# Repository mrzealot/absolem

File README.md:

# Absolem

A flat, minimalistic, ergonomic, 36-key keyboard layout.
Read about it at the [intro blogpost](https://zealot.hu/absolem), or come join the [Discord "clubhouse"](https://discord.gg/DbCfZfZ)!

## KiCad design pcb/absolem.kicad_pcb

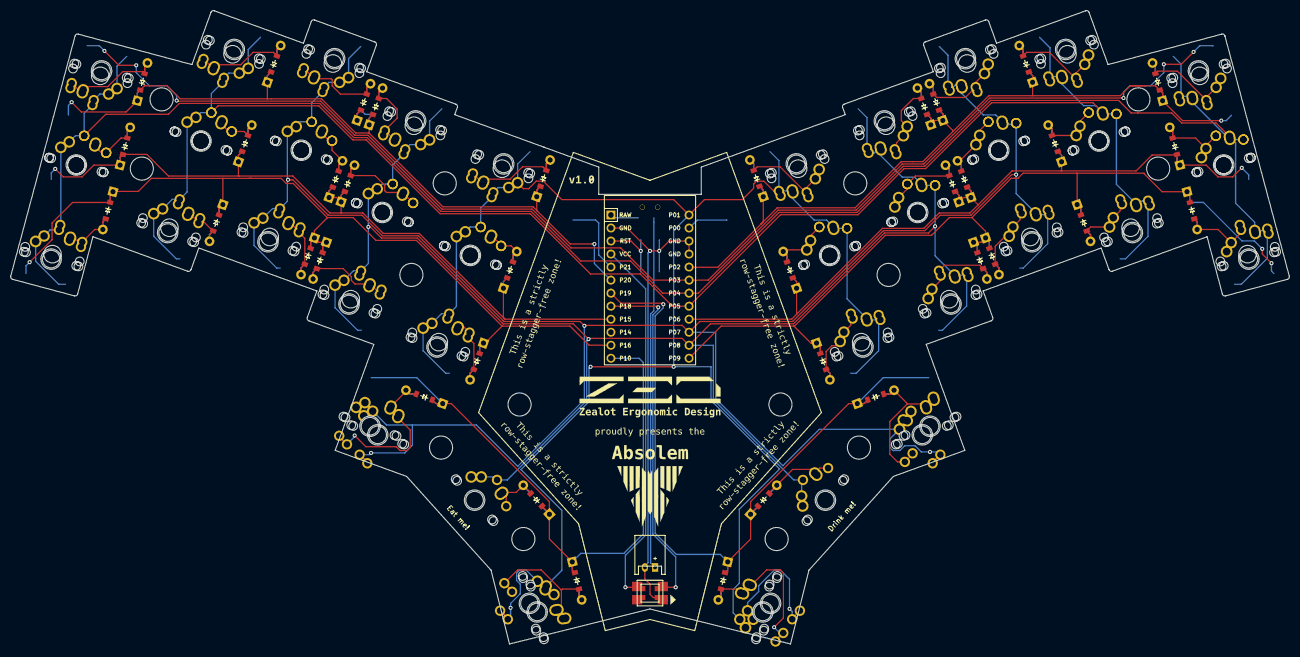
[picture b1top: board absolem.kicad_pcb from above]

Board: 2 copper layers, 249.4 x 123.5 mm, 225 parts (0 on the bottom side), 58 nets.

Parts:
B1: SW_TACT_ALPS_SKQGABE010
C1: ProMicro
D1, D2, D3, D4, D5, D6, D7, D8, D9, D10, D11, D12, D13, D14, D15, D16, D17, D18, D19, D20, D21, D22, D23, D24, D25, D26, D27, D28, D29, D30, D31, D32, D33, D34, D35, D36: ComboDiode
GBACK: LOGO
GFRONT: LOGO
J1: JST_PH_S2B-PH-K_02x2.00mm_Angled
L1: WS2812B
P1, P2, P3, P4, P5, P6, P7, P8, P9, P10, P11, P12, P13, P14, P15, P16, P17, P18, P19, P20, P21, P22, P23, P24, P25, P26, P27, P28, P29, P30, P31, P32: SMDPad
S1, S4, S7, S10, S13, S16, S19, S22, S25, S28, S31, S34, S37, S40, S43, S61, S64, S67, S70, S73, S76, S79, S82, S85, S88, S91, S94, S97, S100, S103, S106, S109, S112, S115, S118, S136, S139, S142, S145, S148: MX
S2, S5, S8, S11, S14, S17, S20, S23, S26, S29, S32, S35, S38, S41, S44, S62, S65, S68, S71, S74, S77, S80, S83, S86, S89, S92, S95, S98, S101, S104, S107, S110, S113, S116, S119, S137, S140, S143, S146, S149: ALPS
S3, S6, S9, S12, S15, S18, S21, S24, S27, S30, S33, S36, S39, S42, S45, S46, S47, S48, S49, S50, S51, S52, S53, S54, S55, S56, S57, S58, S59, S60, S63, S66, S69, S72, S75, S78, S81, S84, S87, S90, S93, S96, S99, S102, S105, S108, S111, S114, S117, S120, S121, S122, S123, S124, S125, S126, S127, S128, S129, S130, S131, S132, S133, S134, S135, S138, S141, S144, S147, S150: PG1350
T1: SPDT_C128955

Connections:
GND: B1.2, C1.2, C1.15, C1.16, J1.2, L1.3, L1.33
P0: C1.14, P32.1
P1: C1.13, P13.1, P14.1, P28.1, P29.1, S37.2, S38.2, S39.2, S40.2, S41.2, S42.2, S43.2, S44.2, S45.2, S58.2, S59.2, S60.2, S67.2, S68.2, S69.2, S70.2, S71.2, S72.2, S112.1, S113.1, S114.1, S115.1, S116.1, S117.1, S118.1, S119.1, S120.1, S133.1, S134.1, S135.1, S142.2, S143.2, S144.2, S145.2, S146.2, S147.2
P2: C1.17, D21.1, D21.2, D24.1, D24.2, D27.1, D27.2, D30.1, D30.2, D33.1, D33.2, P19.1
P3: C1.18, P6.1, P21.1
P4: C1.19, P2.1, P5.1, P17.1, P20.1, S1.2, S2.2, S3.2, S4.2, S5.2, S6.2, S7.2, S8.2, S9.2, S46.2, S47.2, S48.2, S76.1, S77.1, S78.1, S79.1, S80.1, S81.1, S82.1, S83.1, S84.1, S121.1, S122.1, S123.1
P5: C1.20, P7.1, P8.1, P22.1, P23.1, S10.2, S11.2, S12.2, S13.2, S14.2, S15.2, S16.2, S17.2, S18.2, S49.2, S50.2, S51.2, S85.1, S86.1, S87.1, S88.1, S89.1, S90.1, S91.1, S92.1, S93.1, S124.1, S125.1, S126.1
P6: C1.21, D20.1, D20.2, D23.1, D23.2, D26.1, D26.2, D29.1, D29.2, D32.1, D32.2, P18.1
P7: C1.22, P9.1, P10.1, P24.1, P25.1, S19.2, S20.2, S21.2, S22.2, S23.2, S24.2, S25.2, S26.2, S27.2, S52.2, S53.2, S54.2, S61.2, S62.2, S63.2, S73.2, S74.2, S75.2, S94.1, S95.1, S96.1, S97.1, S98.1, S99.1, S100.1, S101.1, S102.1, S127.1, S128.1, S129.1, S136.2, S137.2, S138.2, S148.2, S149.2, S150.2
P8: C1.23, P11.1, P12.1, P26.1, P27.1, S28.2, S29.2, S30.2, S31.2, S32.2, S33.2, S34.2, S35.2, S36.2, S55.2, S56.2, S57.2, S64.2, S65.2, S66.2, S103.1, S104.1, S105.1, S106.1, S107.1, S108.1, S109.1, S110.1, S111.1, S130.1, S131.1, S132.1, S139.2, S140.2, S141.2
P9: C1.24, D19.1, D19.2, D22.1, D22.2, D25.1, D25.2, D28.1, D28.2, D31.1, D31.2, P16.1
P10: C1.12, D16.1, D16.2, D17.1, D17.2, D18.1, D18.2, P15.1
P15: C1.9, D2.1, D2.2, D5.1, D5.2, D8.1, D8.2, D11.1, D11.2, D14.1, D14.2, P3.1
P16: C1.11, D1.1, D1.2, D4.1, D4.2, D7.1, D7.2, D10.1, D10.2, D13.1, D13.2, P1.1
P18: C1.8, L1.4, L1.44
P19: C1.7, D34.1, D34.2, D35.1, D35.2, D36.1, D36.2, P30.1
P20: C1.6, D3.1, D3.2, D6.1, D6.2, D9.1, D9.2, D12.1, D12.2, D15.1, D15.2, P4.1
P21: C1.5, P31.1
RAW: C1.1, T1.1
RAWER: J1.1, T1.2
RST: B1.1, C1.3
VCC: C1.4, L1.1, L1.11
far_thumb: D18.1, D18.2, S67.1, S68.1, S69.1, S70.1, S71.1, S72.1
home_thumb: D17.1, D17.2, S64.1, S65.1, S66.1
index_bottom: D10.1, D10.2, S28.1, S29.1, S30.1, S55.1
index_home: D11.1, D11.2, S31.1, S32.1, S33.1, S56.1
index_top: D12.1, D12.2, S34.1, S35.1, S36.1, S57.1
inner_bottom: D13.1, D13.2, S37.1, S38.1, S39.1, S58.1
inner_home: D14.1, D14.2, S40.1, S41.1, S42.1, S59.1
inner_top: D15.1, D15.2, S43.1, S44.1, S45.1, S60.1
middle_bottom: D7.1, D7.2, S19.1, S20.1, S21.1, S52.1
middle_home: D8.1, D8.2, S22.1, S23.1, S24.1, S53.1
middle_top: D9.1, D9.2, S25.1, S26.1, S27.1, S54.1
mirror_far_thumb: D36.1, D36.2, S142.1, S143.1, S144.1, S145.1, S146.1, S147.1
mirror_home_thumb: D35.1, D35.2, S139.1, S140.1, S141.1
mirror_index_bottom: D28.1, D28.2, S103.2, S104.2, S105.2, S130.2
mirror_index_home: D29.1, D29.2, S106.2, S107.2, S108.2, S131.2
mirror_index_top: D30.1, D30.2, S109.2, S110.2, S111.2, S132.2
mirror_inner_bottom: D31.1, D31.2, S112.2, S113.2, S114.2, S133.2
mirror_inner_home: D32.1, D32.2, S115.2, S116.2, S117.2, S134.2
mirror_inner_top: D33.1, D33.2, S118.2, S119.2, S120.2, S135.2
mirror_middle_bottom: D25.1, D25.2, S94.2, S95.2, S96.2, S127.2
mirror_middle_home: D26.1, D26.2, S97.2, S98.2, S99.2, S128.2
mirror_middle_top: D27.1, D27.2, S100.2, S101.2, S102.2, S129.2
mirror_near_thumb: D34.1, D34.2, S136.1, S137.1, S138.1, S148.1, S149.1, S150.1
mirror_pinky_bottom: D19.1, D19.2, S76.2, S77.2, S78.2, S121.2
mirror_pinky_home: D20.1, D20.2, S79.2, S80.2, S81.2, S122.2
mirror_pinky_top: D21.1, D21.2, S82.2, S83.2, S84.2, S123.2
mirror_ring_bottom: D22.1, D22.2, S85.2, S86.2, S87.2, S124.2
mirror_ring_home: D23.1, D23.2, S88.2, S89.2, S90.2, S125.2
mirror_ring_top: D24.1, D24.2, S91.2, S92.2, S93.2, S126.2
near_thumb: D16.1, D16.2, S61.1, S62.1, S63.1, S73.1, S74.1, S75.1
pinky_bottom: D1.1, D1.2, S1.1, S2.1, S3.1, S46.1
pinky_home: D2.1, D2.2, S4.1, S5.1, S6.1, S47.1
pinky_top: D3.1, D3.2, S7.1, S8.1, S9.1, S48.1
ring_bottom: D4.1, D4.2, S10.1, S11.1, S12.1, S49.1
ring_home: D5.1, D5.2, S13.1, S14.1, S15.1, S50.1
ring_top: D6.1, D6.2, S16.1, S17.1, S18.1, S51.1

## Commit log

2018-09-09 Initial CAD model
2018-09-10 Fix screw holes + remove original code from generated .scad files
2018-09-12 Fix thumb plate
2019-04-29 Reconsider polygon approach
2019-04-29 Absolem first draft
2019-05-30 Mid-refactor
2019-06-14 Getting there... eventually
2019-06-15 Inner contour finished + logo started
2019-06-16 Logo done + screw holes done + usb hole started
2019-06-16 Started a re-refactor...
2019-06-17 Almost there...
2019-06-19 Mat, illustration, minor belly fixes
2019-06-19 Minor mat fix
2019-06-19 Logo refactor + badge started
2019-06-20 Badge progress
2019-06-24 First revision done
2019-06-26 Cleanup + QC fixes
2019-07-07 Talked a lot with Dan, turns out I'm not done...
2019-07-08 Redesign done
2019-07-09 Minor reorg
2019-07-09 Initial firmware structure
2019-08-01 A huge chunk of firmware groundwork
2019-08-01 Minor plan changes
2019-08-01 First draft of the blogpost
2019-08-11 First working version
2019-08-11 A few notes about the battery and the firmware
2019-08-17 Minor change in where plan output is generated
2019-08-17 Matrix debugging and module progress
2019-08-18 Debug macroization + basic module functionality
2019-08-18 Modules get static names and can now break notify chains
2019-08-18 Cache module for deterministic releases
2019-08-18 Keycodes + first keymap test
2019-08-18 Small failsafe for the queue
2019-08-24 Profiling + Interpreter optimization
2019-08-25 Make physical keys 1-based
2019-08-25 Avoid the potential mixing of event batches
2019-08-25 Basic layer functionality
2019-08-26 MultiTrigger pre-debug
2019-08-26 Discount tapdance is alive
2019-08-29 Replicated QMK keymap
2019-08-29 Minor keymap fixes
2019-08-29 Started work on the writeup
2019-08-29 Writeup progress
2019-08-29 Research section done
2019-08-29 Various writeup progress
2019-09-01 Etimology and future work progress
2019-09-02 Sentence line breaks + minor fixes
2019-09-03 Build progress
2019-09-03 Logo progress
2019-09-04 Styling test
2019-09-04 Fun pics + minor mods
2019-09-04 Formatting
2019-09-04 Pic shrinking
2019-09-05 Polygon pics
2019-09-05 Transitioning to 2D
2019-09-05 Finished pics + various progress
2019-09-06 Wireless + Low Profile Police done
2019-09-06 Image size adjustments
2019-09-06 Firmware first draft
2019-09-06 Pic restructure
2019-09-06 Assembly pics added
2019-09-07 Assembly first draft
2019-09-07 Wiring first draft
2019-09-07 Minor footnote + contact mods
2019-09-07 Spell check
2019-09-07 Minor corrections
2019-09-07 Reddit link feedback
2019-09-07 ErgoWarp correction
2019-09-13 Battery reporting + robustizing
2019-09-14 Battery reporting debug
2019-09-17 Implement sleep + low tick mode
2019-09-20 Extract firmware to its own repo
2020-02-05 Keymap drive link changed + relative splash href
2020-05-26 MK2 refactor started
2020-05-28 Matrix points
2020-05-29 A shitton of points progress
2020-05-30 Points practically done
2020-05-31 Point fixes and asymmetry tests
2020-05-31 Outline progress
2020-06-03 Outline progress and getting stuck
2020-06-06 Basic outlining done
2020-06-25 Fixed firmware link + added favicon
2020-06-28 Remaining mods
2020-06-28 Favicon fix
2020-06-28 Favicon and styling fix
2020-06-28 Club-related updates
2020-07-21 Post-ergogen restructure
2020-07-21 Add initial config + generated raw PCB
2020-07-22 Pin remapping for a more elegant layout
2020-07-22 Routing done
2020-07-23 First PCB release candidate
2020-07-24 Easter eggs + minor metadata fix
2020-08-16 Update config to newer ergogen version
2020-09-06 First pass at the new switchplate
2020-09-21 Plates done
2020-10-08 First version of classic MX cases
2020-10-09 Added missing USB cutout
2020-10-17 Update config to newer ergogen dialect
2021-01-01 Ergogen refactor config update
2021-02-18 Ergogen preprocessor update
2021-04-18 Mk3 brainstorming...
2021-09-12 Updated absolem.yaml
    Updated it so it can now be used with the Ergogen online thingie without errors
2021-12-31 case files and readme
